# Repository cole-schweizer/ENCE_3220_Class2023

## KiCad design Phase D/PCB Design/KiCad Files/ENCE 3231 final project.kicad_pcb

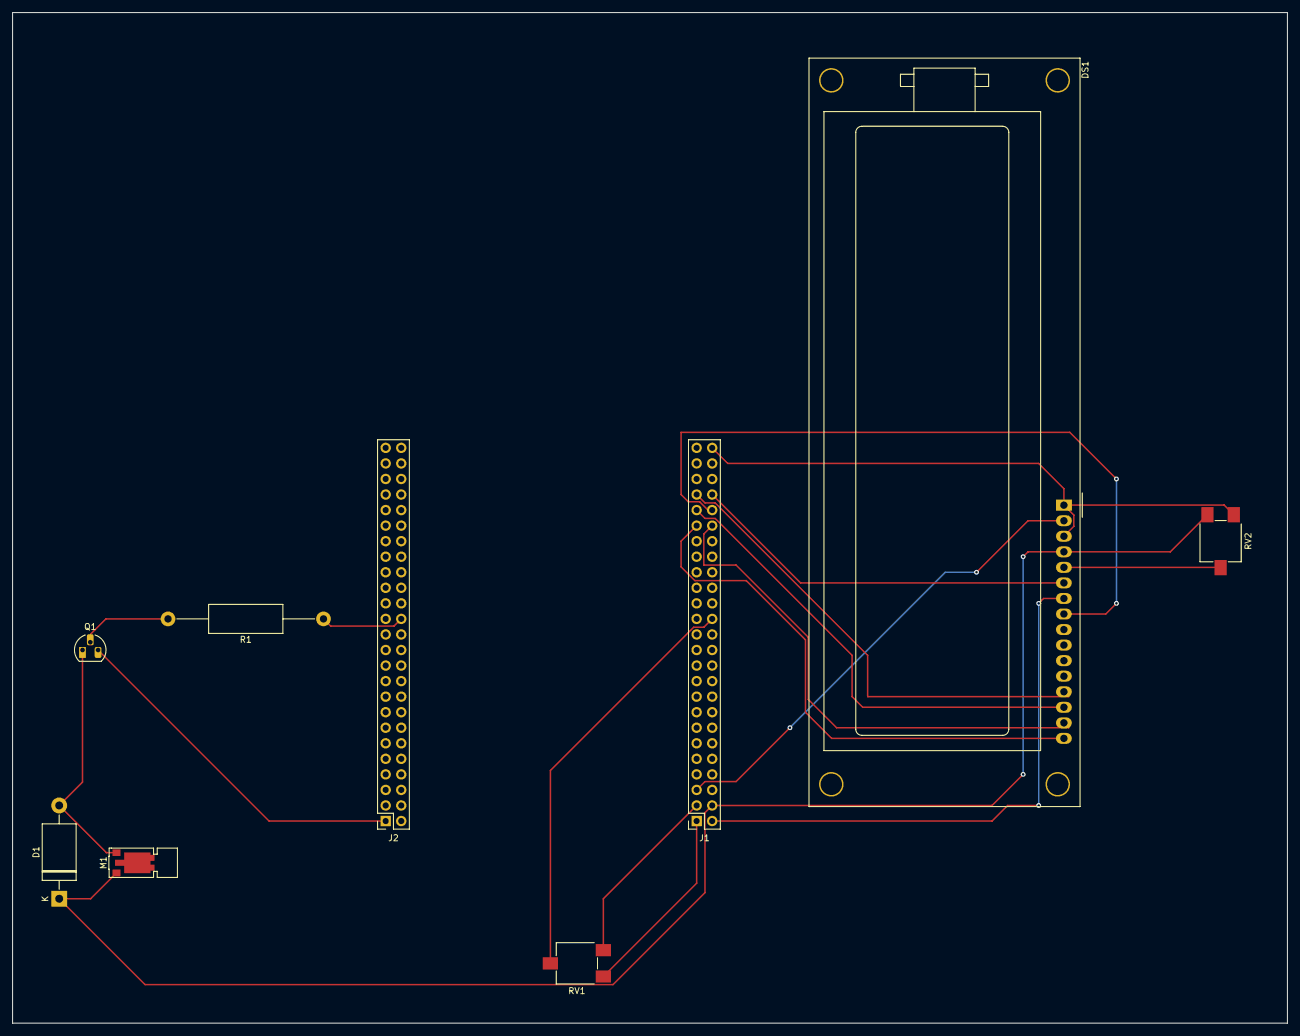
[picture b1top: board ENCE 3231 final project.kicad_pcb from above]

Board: 2 copper layers, 208.3 x 165.1 mm, 9 parts (0 on the bottom side), 14 nets.

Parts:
D1: 1.5KExxA; D_DO-201AE_P15.24mm_Horizontal
DS1: HY1602E
J1: Discovery Board Conn 2; PinSocket_2x25_P2.54mm_Vertical
J2: Discovery Board Conn 1; PinSocket_2x25_P2.54mm_Vertical
M1: Motor_DC; Vybronics_VZ30C1T8219732L
Q1: NPN; TO-92L_HandSolder
R1: R_Small; R_Axial_DIN0414_L11.9mm_D4.5mm_P25.40mm_Horizontal
RV1, RV2: R_Potentiometer; Potentiometer_ACP_CA6-VSMD_Vertical

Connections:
3.3V: DS1.2 (LEDA), J1.5
5V: D1.1 (A1), DS1.4 (VDD), J1.3, J1.4, M1.1 (+), RV1.1, RV2.1
D4: DS1.13 (DB4), J1.43
D5: DS1.14 (DB5), J1.41
D6: DS1.15 (DB6), J1.40
D7: DS1.16 (DB7), J1.39
E: DS1.8 (E), J1.42
GND: DS1.1 (LEDK), DS1.3 (VSS), DS1.7 (R/~W), J1.1, J1.2, J1.49, J1.50, J2.1, J2.2, J2.49, J2.50, Q1.3 (E), RV1.3, RV2.3
Input_Signal: J1.28, RV1.2
Motor_PWM: J2.28, R1.1
unnamed: D1.2 (A2), M1.2 (-), Q1.1 (C)
unnamed: DS1.5 (Vo), RV2.2
unnamed: Q1.2 (B), R1.2
Rs: DS1.6 (RS), J1.44

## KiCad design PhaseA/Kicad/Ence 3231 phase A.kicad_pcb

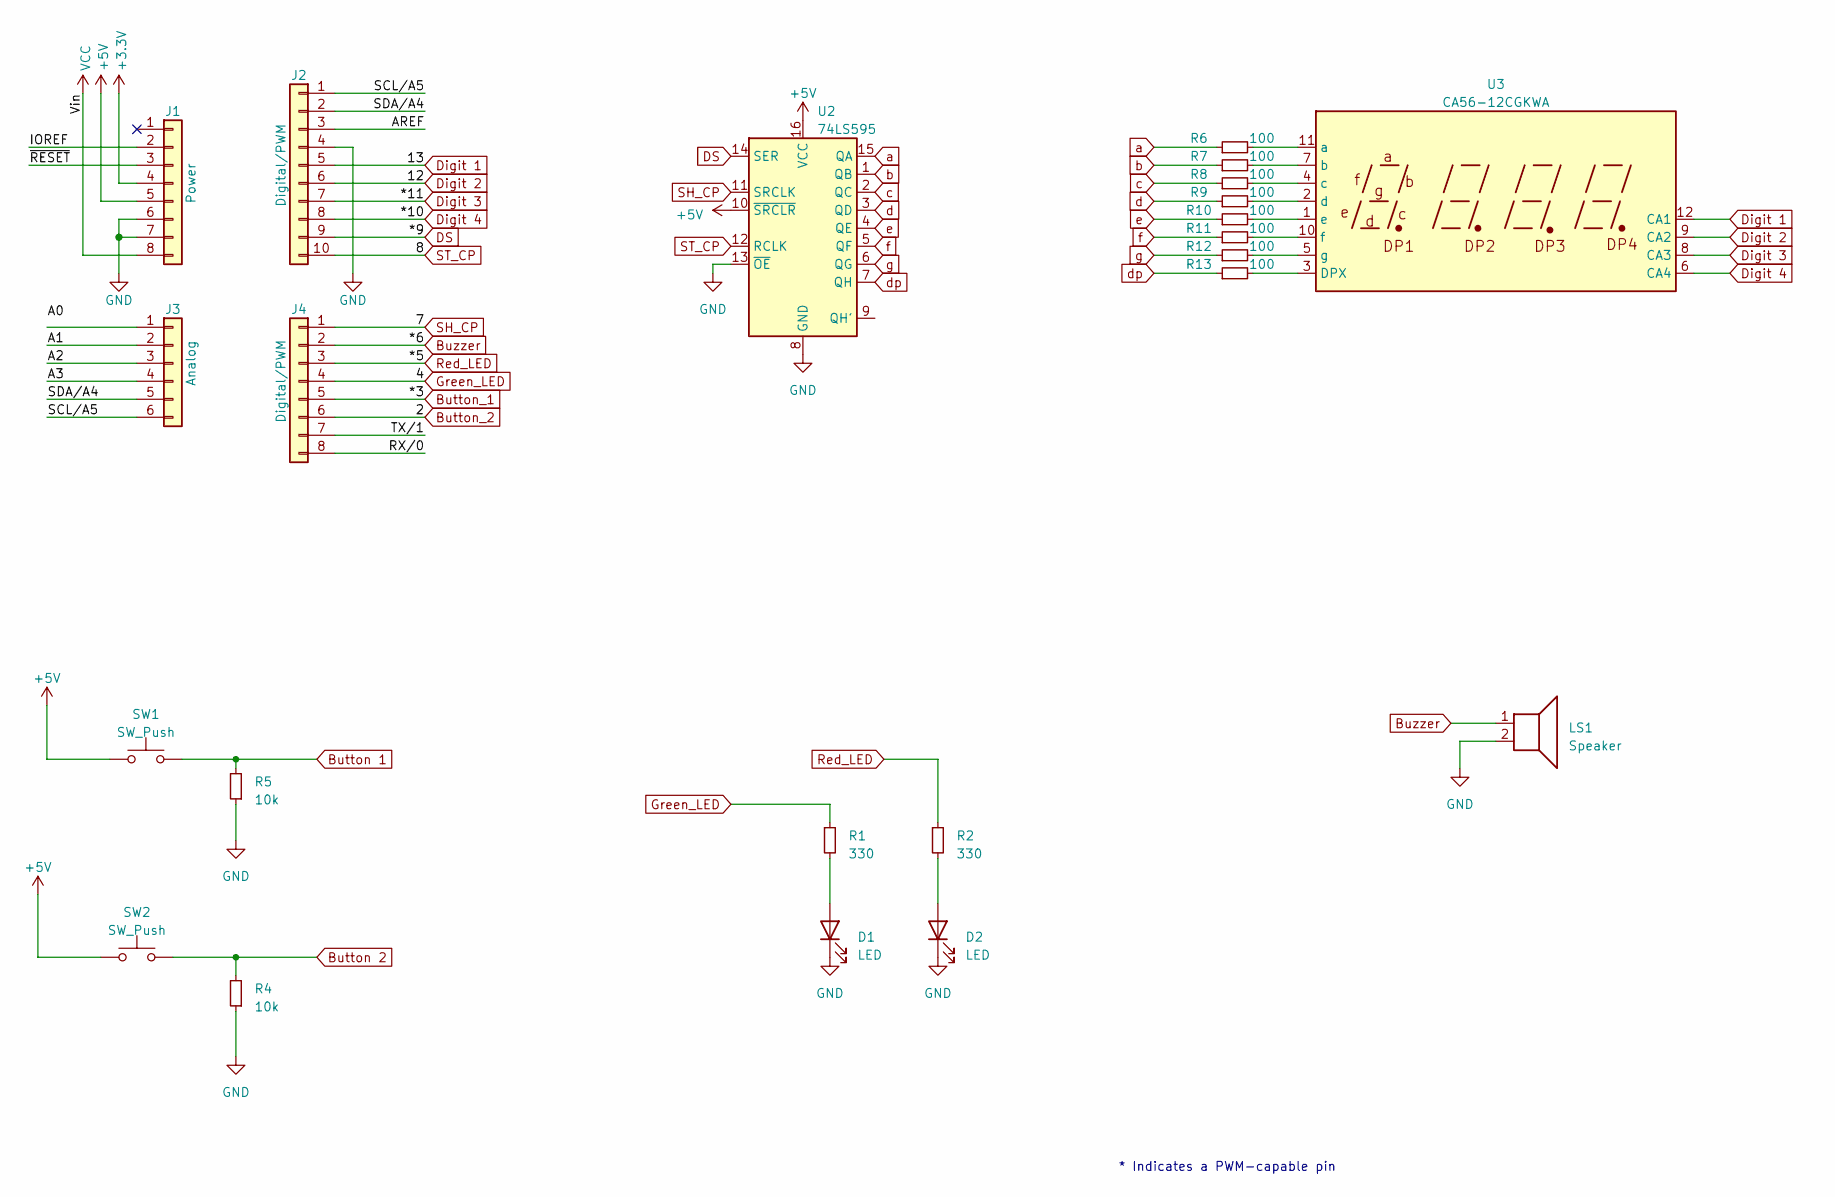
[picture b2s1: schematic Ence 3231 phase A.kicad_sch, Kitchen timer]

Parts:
D1, D2: LED; LED_D3.0mm
J1: Power; PinSocket_1x08_P2.54mm_Vertical
J2: Digital/PWM; PinSocket_1x10_P2.54mm_Vertical
J3: Analog; PinSocket_1x06_P2.54mm_Vertical
J4: Digital/PWM; PinSocket_1x08_P2.54mm_Vertical
LS1: Speaker; Buzzer_12x9.5RM7.6
R1, R2: 330; R_Axial_DIN0204_L3.6mm_D1.6mm_P5.08mm_Horizontal
R4, R5: 10k; R_Axial_DIN0204_L3.6mm_D1.6mm_P5.08mm_Horizontal
R6, R7, R8, R9, R10, R11, R12, R13: 100; R_Axial_DIN0204_L3.6mm_D1.6mm_P5.08mm_Horizontal
SW1, SW2: SW_Push; SW_PUSH_6mm_H5mm
U2: 74LS595; DIP-16_W7.62mm_Socket
U3: CA56-12CGKWA

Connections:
+3V3: J1.4
+5V: J1.5, SW1.1, SW2.1, U2.10 (~SRCLR), U2.16 (VCC)
/A1: J3.2
/A2: J3.3
/A3: J3.4
/AREF: J2.3
/IOREF: J1.2
/RX/0: J4.8
/SCL/A5: J2.1, J3.6
/SDA/A4: J2.2, J3.5
/TX/1: J4.7
/~RESET: J1.3
Button 1: R5.2, SW1.2
Button 2: R4.2, SW2.2
Button_1: J4.5
Button_2: J4.6
Buzzer: J4.2, LS1.1
DS: J2.9, U2.14 (SER)
Digit 1: J2.5, U3.12 (CA1)
Digit 2: J2.6, U3.9 (CA2)
Digit 3: J2.7, U3.8 (CA3)
Digit 4: J2.8, U3.6 (CA4)
GND: D1.1 (K), D2.1 (K), J1.6, J1.7, J2.4, LS1.2, R4.1, R5.1, U2.8 (GND), U2.13 (~OE)
Green_LED: J4.4, R1.1
unnamed: D1.2 (A), R1.2
unnamed: D2.2 (A), R2.2
unnamed: R13.2, U3.3 (DPX)
unnamed: R6.2, U3.11 (a)
unnamed: R7.2, U3.7 (b)
unnamed: R8.2, U3.4 (c)
unnamed: R9.2, U3.2 (d)
unnamed: R10.2, U3.1 (e)
unnamed: R11.2, U3.10 (f)
unnamed: R12.2, U3.5 (g)
Red_LED: J4.3, R2.1
SH_CP: J4.1, U2.11 (SRCLK)
ST_CP: J2.10, U2.12 (RCLK)
VCC: J1.8
a: R6.1, U2.15 (QA)
b: R7.1, U2.1 (QB)
c: R8.1, U2.2 (QC)
d: R9.1, U2.3 (QD)
dp: R13.1, U2.7 (QH)
e: R10.1, U2.4 (QE)
f: R11.1, U2.5 (QF)
g: R12.1, U2.6 (QG)

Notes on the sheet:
* Indicates a PWM-capable pin

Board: 2 copper layers, 27 parts (0 on the bottom side), 34 nets, no tracks yet.

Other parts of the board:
MH1, MH2, MH3, MH4: MountingHole_3.2mm

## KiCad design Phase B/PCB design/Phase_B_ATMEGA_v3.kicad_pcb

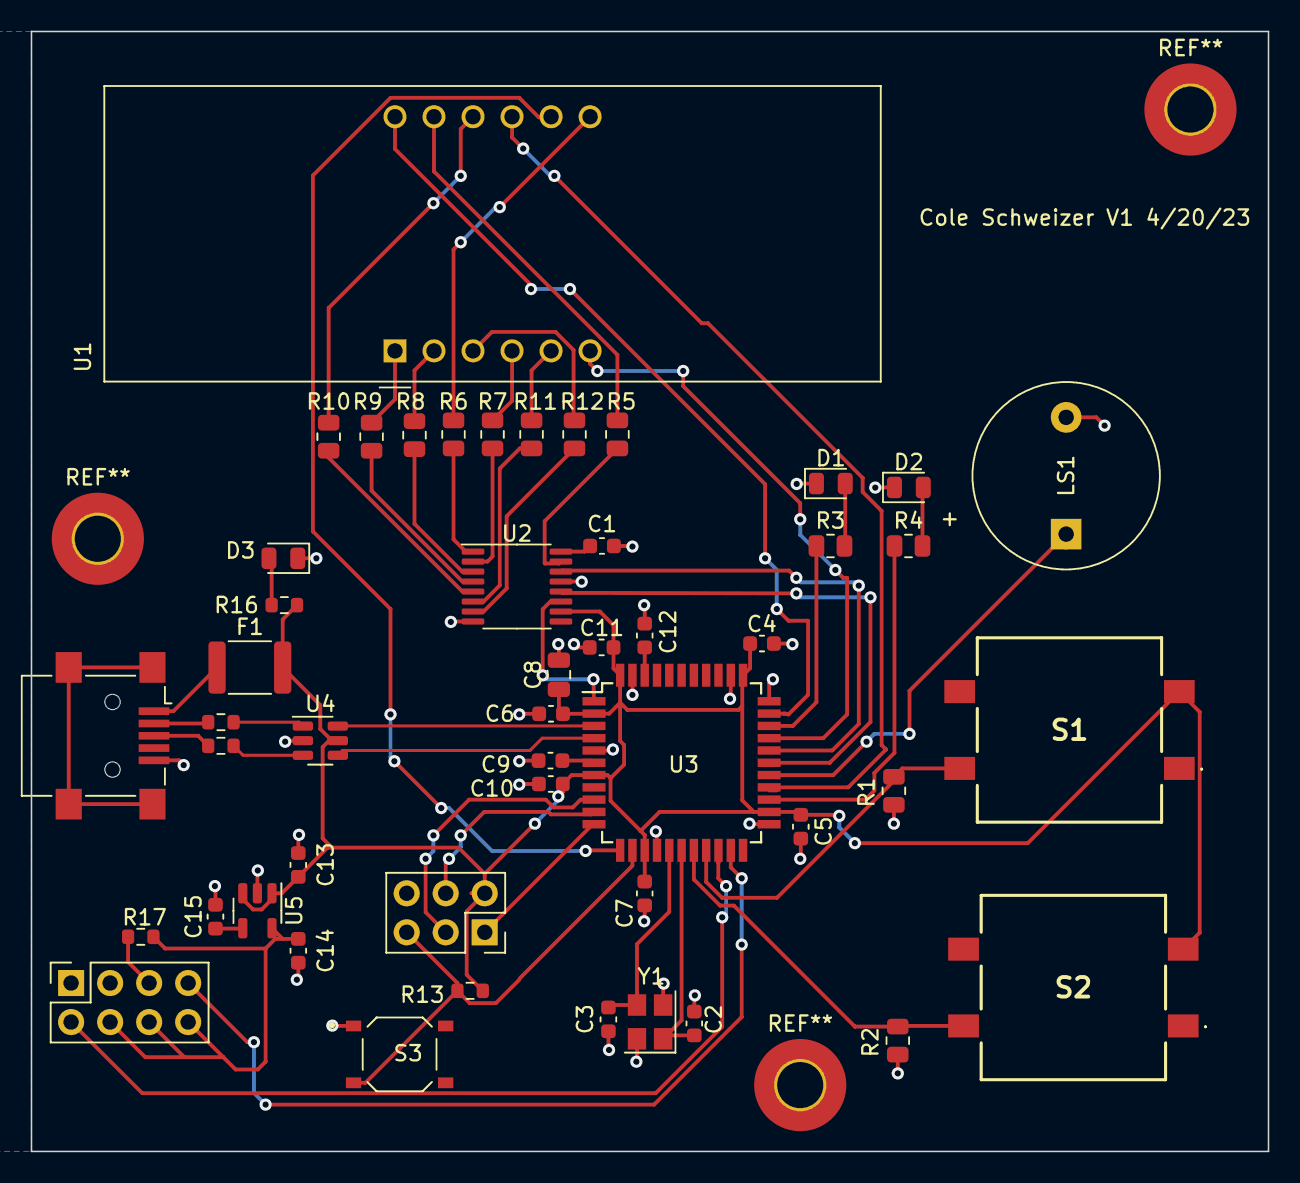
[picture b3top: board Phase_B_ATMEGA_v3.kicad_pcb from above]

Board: 2 copper layers, 80.5 x 72.9 mm, 49 parts (0 on the bottom side), 53 nets.

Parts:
C1: 0.1u; C_0603_1608Metric
C2, C3: 22p; C_0603_1608Metric
C4, C5, C6, C7, C10, C11, C12: 0.1uF; C_0603_1608Metric
C8: 10uF; C_0805_2012Metric
C9, C13: 1uF; C_0603_1608Metric
C14: 2.2uF; C_0603_1608Metric
C15: 10nF; C_0603_1608Metric
D1, D2, D3: LED; LED_0805_2012Metric
F1: PTCSMD; Fuse_1812_4532Metric
J1: AVR-ISP-6; PinSocket_2x03_P2.54mm_Vertical
J2: USB_B_Mini; USB_Mini-B_Lumberg_2486_01_Horizontal
J3: ESP_Conn; PinSocket_2x04_P2.54mm_Vertical
LS1: Speaker; Buzzer_12x9.5RM7.6
R1, R2: 10k; R_0805_2012Metric
R3, R4: 330; R_0805_2012Metric
R5, R6, R7, R8, R9, R10, R11, R12: 100; R_0805_2012Metric
R13, R17: 10k; R_0603_1608Metric
R14, R15: 22; R_0603_1608Metric
R16: 1k; R_0603_1608Metric
S1, S2: PTS125SM43SMTR21M_LFS; PTS125_SMD_Button
S3: PTS526_SM08_SMTR2_LFS; PTS526_SMD_Button
U1: CA56-12EWA
U2: 74HC595; TSSOP-16_4.4x5mm_P0.65mm
U3: ATmega32U4-A; TQFP-44_10x10mm_P0.8mm
U4: USBLC6-2SC6; SOT-23-6
U5: LP2985-3.3; SOT-23-5
Y1: 16MHz; Crystal_SMD_Abracon_ABM8G-4Pin_3.2x2.5mm

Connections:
+3.3V: C14.1, J3.4, J3.6, J3.8, R17.1, U5.5 (VOUT)
+5V: C1.1, C4.1, C5.1, C6.1, C7.1, C8.1, C10.1, C11.1, C13.1, F1.2, J1.2 (VCC), R13.1, R16.1, S1.C1 (COM_1), S2.C1 (COM_1), U2.10 (~SRCLR), U2.16 (VCC), U3.2 (UVCC), U3.7 (VBUS), U3.14 (VCC), U3.24 (AVCC), U3.34 (VCC), U3.44 (AVCC), U4.5 (VBUS), U5.1 (VIN), U5.3 (ON/~OFF)
/AREF: C12.1, U3.42 (AREF)
/UCAP: C9.1, U3.6 (UCAP)
Button_1: R1.1, S1.B1 (NO_2), U3.19 (PD1)
Button_2: R2.1, S2.B1 (NO_2), U3.18 (PD0)
Buzzer: LS1.1, U3.27 (PD7)
DS: U2.14 (SER), U3.29 (PB5)
Dig1: U1.12 (CA1), U3.32 (PC7)
Dig2: U1.9 (CA2), U3.26 (PD6)
Dig3: U1.8 (CA3), U3.12 (PB7)
Dig4: U1.6 (CA4), U3.30 (PB6)
GND: C1.2, C2.1, C3.2, C4.2, C5.2, C6.2, C7.2, C8.2, C9.2, C10.2, C11.2, C12.2, C13.2, C14.2, C15.2, D1.1 (K), D2.1 (K), D3.1 (K), J1.6 (GND), J2.5 (GND), J3.1, LS1.2, R1.2, R2.2, S3.1, U2.8 (GND), U2.13 (~OE), U3.5 (UGND), U3.15 (GND), U3.23 (GND), U3.33 (~HWB/PE2), U3.35 (GND), U3.43 (GND), U4.2 (GND), U5.2 (GND), Y1.2, Y1.4
GREEN_LED: R4.1, U3.25 (PD4)
MISO: J1.1 (MISO), U3.11 (PB3)
MOSI: J1.4 (MOSI), U3.10 (PB2)
unnamed: D1.2 (A), R3.2
unnamed: D2.2 (A), R4.2
unnamed: D3.2 (A), R16.2
unnamed: J2.3 (D+), R14.1
unnamed: J2.2 (D-), R15.1
unnamed: F1.1, J2.1 (VBUS)
unnamed: J3.5, R17.2
unnamed: R12.2, U1.3 (DPX)
unnamed: R5.2, U1.11 (a)
unnamed: R6.2, U1.7 (b)
unnamed: R7.2, U1.4 (c)
unnamed: R8.2, U1.2 (d)
unnamed: R9.2, U1.1 (e)
unnamed: R10.2, U1.10 (f)
unnamed: R11.2, U1.5 (g)
unnamed: C15.1, U5.4 (BP)
RED_LED: R3.1, U3.31 (PC6)
RST: J1.5 (~RST), R13.2, S3.3, U3.13 (~RESET)
RX: J3.7, U3.21 (PD3)
SCK: J1.3 (SCK), U3.9 (PB1)
SH_CP: U2.11 (SRCLK), U3.1 (PE6)
ST_CP: U2.12 (RCLK), U3.28 (PB4)
TX: J3.2, U3.20 (PD2)
USB_CONN_D+: R14.2, U4.3 (I/O2)
USB_CONN_D-: R15.2, U4.1 (I/O1)
USB_D+: U3.4 (D+), U4.4 (I/O2)
USB_D-: U3.3 (D-), U4.6 (I/O1)
XTAL1: C2.2, U3.17 (XTAL1), Y1.1
XTAL2: C3.1, U3.16 (XTAL2), Y1.3
a: R5.1, U2.15 (QA)
b: R6.1, U2.1 (QB)
c: R7.1, U2.2 (QC)
d: R8.1, U2.3 (QD)
dp: R12.1, U2.7 (QH)
e: R9.1, U2.4 (QE)
f: R10.1, U2.5 (QF)
g: R11.1, U2.6 (QG)

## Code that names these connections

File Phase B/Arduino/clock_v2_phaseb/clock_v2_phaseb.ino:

#define BUTTON_2  2  
#define BUTTON_1  3  
#define GREEN_LED 4
#define RED_LED   5
#define BUZZER    6

#define DATA      9 // DS
#define LATCH     8 // ST_CP
#define CLOCK     7 // SH_CP

#define DIGIT_4   10
#define DIGIT_3   11
#define DIGIT_2   12
#define DIGIT_1   13

#define LED 13
#define BUFF_SIZE 20

#define DEFAULT_COUNT 30 // default value is 30secs

// 7-Seg Display Variables
unsigned char gtable[]=
{0x3f,0x06,0x5b,0x4f,0x66,0x6d,0x7d,0x07,0x7f,0x6f,0x77,0x7c
,0x39,0x5e,0x79,0x71,0x00};
byte gCurrentDigit;

// Volatile Variables
volatile unsigned char gISRFlag1 = 0;
volatile unsigned char gBuzzerFlag = 0;
volatile unsigned char gISRFlag2 = 0;
volatile unsigned char gbuttonISR1 = 0;
volatile unsigned char gbuttonISR2 = 0;
volatile int  gCount = DEFAULT_COUNT;

// Timer Variables
unsigned char gTimerRunning = 0; 
unsigned int gReloadTimer1 = 62500; // corresponds to 1 second
unsigned int gReloadTimer2 = 100;
byte gReloadTimerDisplay = 10;  // display refresh time
char gIncomingChar;
char gCommMsg[BUFF_SIZE];
int buff = 0;
byte gPackageFlag = 0;
byte gProcessFlag = 0;


void setup() {
   // LEDs Pins
  pinMode(RED_LED, OUTPUT);
  pinMode(GREEN_LED, OUTPUT);

  // LEDs -> Timer Stopped
  digitalWrite(RED_LED, HIGH);
  digitalWrite(GREEN_LED, HIGH);

  // Button Pins
  pinMode(BUTTON_1, INPUT_PULLUP);
  attachInterrupt(digitalPinToInterrupt(BUTTON_1), gbuttonISR1, RISING);
  pinMode(BUTTON_2, INPUT_PULLUP);
  attachInterrupt(digitalPinToInterrupt(BUTTON_2), gbuttonISR2, RISING);

  // Buzer Pins
  pinMode(BUZZER, OUTPUT);

  // Buzzer -> Off
  digitalWrite(BUZZER,LOW);

  // 7-Seg Display
  pinMode(DIGIT_1, OUTPUT);
  pinMode(DIGIT_2, OUTPUT);
  pinMode(DIGIT_3, OUTPUT);
  pinMode(DIGIT_4, OUTPUT);

  // Shift Register Pins
  pinMode(LATCH, OUTPUT);
  pinMode(CLOCK, OUTPUT);
  pinMode(DATA, OUTPUT);

  dispOff();  // turn off the display
  pinMode(LED, OUTPUT); //declare led as an output
  Serial.begin(9600); //baud rate of 9600

  // Initialize Timer1
  // Speed of Timer1 = 16MHz/64 = 250 KHz
  TCCR1A = 0;
  TCCR1B = 0;
  OCR1A = gReloadTimer1;            // max value 2^16 - 1 = 65535
  TCCR1A |= (1<<WGM11);
  TCCR1B = (1<<CS11) | (1<<CS10);   // 64 prescaler
  TIMSK1 |= (1<<OCIE1A);
  interrupts(); 
}
void display(unsigned char num, unsigned char dp){
  digitalWrite(LATCH, LOW);
  shiftOut(DATA, CLOCK, MSBFIRST, gtable[num] | (dp<<7));
  digitalWrite(LATCH, HIGH);
}
//used to compare two arrays of chars to see if equal
char compareMsg(char a[], char b[], int size){
  int i; 
  char result;

  for(i = 0;  i < size; i++){
    if(a[i] != b[i]){
      result = 0; //arrays not equal
    }else{
      result = 1; //arrays are equal
    }
  } 
  return result;
} 
//interrupt routine to read data from ESP
ISR(TIMER_COMPA_vect){ 
  if(Serial.available()>0){
    gISRFlag2 = 1;
  }
}
void dispOff(){
   digitalWrite(DIGIT_1, HIGH);
   digitalWrite(DIGIT_2, HIGH);
   digitalWrite(DIGIT_3, HIGH);
   digitalWrite(DIGIT_4, HIGH);
}
void buttonISR2(){
  //increment clock
  gCount++;
}
void buttonISR1(){ 
  // Set ISR Flag
  gISRFlag1 = 1;
}

// Timer2 interrupt service routine (ISR)
ISR(TIMER2_COMPA_vect) {
  dispOff();  // turn off the display
  OCR2A = gReloadTimer2;  // load timer
 
  switch (gCurrentDigit) {
    case 1: //0x:xx
      display( int((gCount/60) / 10) % 6, 0 );   // prepare to display digit 1 (most left)
      digitalWrite(DIGIT_1, LOW);  // turn on digit 1
      break;
 
    case 2: //x0:xx
      display( int(gCount / 60) % 10, 1 );   // prepare to display digit 2
      digitalWrite(DIGIT_2, LOW);     // turn on digit 2
      break;
 
    case 3: //xx:0x
      display( (gCount / 10) % 6, 0 );   // prepare to display digit 3
      digitalWrite(DIGIT_3, LOW);    // turn on digit 3
      break;
 
    case 4: //xx:x0
      display(gCount % 10, 0); // prepare to display digit 4 (most right)
      digitalWrite(DIGIT_4, LOW);  // turn on digit 4
      break;

    default:
      break;
  }
  gCurrentDigit = (gCurrentDigit % 4) + 1;
}

// Timer1 interrupt service routine (ISR)
ISR(TIMER1_COMPA_vect){
  gCount--;
  OCR1A = gReloadTimer1;

  if(gCount == 0) {
      // Stop Timer
      stopTimer1();
      
      // Raise Alarm
      gBuzzerFlag = 1;
      gTimerRunning = 0;
  }
}
void stopTimer1(){
  // Stop Timer
  TCCR1B = 0; // stop clock
  TIMSK1 = 0; // cancel clock timer interrupt
}
void startTimer1(){
  // Initialize Timer1 (16bit) -> Used for clock
  // Speed of Timer1 = 16MHz/256 = 62.5 KHz
  noInterrupts();
  TCCR1A = 0;
  TCCR1B = 0;
  OCR1A = gReloadTimer1; // compare match register 16MHz/256
  TCCR1B |= (1<<WGM12);   // CTC mode
  TCCR1B |= (1<<CS12);    // 256 prescaler 
  TIMSK1 |= (1<<OCIE1A);  // enable timer compare interrupt
  interrupts();
}
void activeBuzzer(){
  unsigned char i;
  unsigned char sleepTime = 1; // ms
  
  for(i=0;i<100;i++){
    digitalWrite(BUZZER,HIGH);
    delay(sleepTime);//wait for 1ms
    digitalWrite(BUZZER,LOW);
    delay(sleepTime);//wait for 1ms
  }
}
void loop() {
  char messageBuff[BUFF_SIZE];
  int auxCount = 0;
  unsigned char auxDigit = '0';


  if(gISRFlag1 == 1 || gISRFlag2 == 1){
    // Reset ISR Flag
    gISRFlag1 = 0;
    gISRFlag2 = 0;

    gIncomingChar = Serial.read(); //read incoming data

    if(gPackageFlag == 1){
      gCommMsg[buff] = gIncomingChar;  //if new message add to buffer and increment size
      buff++; 

      if(buff == BUFF_SIZE){
        gPackageFlag = 0; //if at max size reset start flag and raise processor flag
        gProcessFlag = 1;
      }
    }
    if(gIncomingChar == '$'){
      gPackageFlag = 1; //if start of msg -> raise flag

      int i;
      for(int i = 0; i<BUFF_SIZE; i++){
        gCommMsg[i] == 0; //set message to 0
      }
      buff = 0; //set msg index to 0
    }

    if((gIncomingChar == '\n') && (gPackageFlag == 1)){
      gPackageFlag = 0; //signal end of msg
      gProcessFlag == 1;
    }
    if(gTimerRunning == 0){
      // Start Timer
      gTimerRunning = 1;

      if(gCount == 0){
        gCount = DEFAULT_COUNT;
      }      
      if(gBuzzerFlag == 1){
        gBuzzerFlag = 0;

        // LEDs -> Timer Stopped
        digitalWrite(RED_LED, HIGH);
        digitalWrite(GREEN_LED, HIGH);
      }
      else
      {
        startTimer1();
        // LEDs -> Timer Running
        digitalWrite(RED_LED, LOW);
        digitalWrite(GREEN_LED, HIGH);
      }
    }
    else
    {
      // Stop Timer
      stopTimer1();
      gTimerRunning = 0;

      // LEDs -> Timer Running
      digitalWrite(RED_LED, HIGH);
      digitalWrite(GREEN_LED, HIGH);
    }
  }
  if(gProcessFlag == 1){
      gProcessFlag = 0; //reset flag

      if(compareMsg(gCommMsg, "STR", 3) == 1){
        digitalWrite(LED, HIGH); //if start signal -> turn LED on
      }
      if(compareMsg(gCommMsg, "STP",3) == 1){
        digitalWrite(LED, LOW); //if stop signal -> turn LED off
      }
      if(compareMsg(gCommMsg, "GET", 3) == 1){
        Serial.print("$00:01\n"); //if get signal -> send clock status
      }
    }


  // Attend gBuzzerFlag
  if(gBuzzerFlag == 1){
    // Make Noise...
    digitalWrite(RED_LED, HIGH);
    digitalWrite(GREEN_LED, LOW);
    activeBuzzer();
  }
}

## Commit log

2023-04-13 Create Read Me
2023-04-13 Create ArduinoCode
2023-04-13 Beta release
2023-04-21 Phase B
2023-06-01 hello
